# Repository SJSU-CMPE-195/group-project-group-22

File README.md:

# (Neuromorphic) Hardware Neural Network

Neuromorphic computing replicates brain structure and function directly in hardware. Unlike conventional processors, it uses parallel, event-driven processing for greater efficiency. Software-based spiking neural networks (SNNs) appear in autonomous control systems but carry high energy and resource costs. This project implements the SNN as a real analog circuit — a physical, transistor-level network built from discrete components on a breadboard or PCB — so the hardware itself is the AI player.

The fundamental building block is a **3-neuron control unit** implementing the integrate-and-fire model: an excitatory neuron and an inhibitory neuron both feed into a control (output) neuron. The excitatory neuron drives the control neuron to fire; the inhibitory neuron suppresses overfiring and improves signal stability. Each control unit produces one discrete game action. This scheme is scalable — Hit The Zone uses one 3-neuron control unit (one game input), and Pong uses two control units (six neurons total, one control unit per direction).

An ESP32 microcontroller acts as the analog bridge between the neuron circuit and the game software: it injects stimulus voltage into the excitatory neuron in response to game state, reads the control neuron's output voltage via ADC, and streams real-time voltage data to a Java application over USB serial at 115200 baud. The Java application detects neural spikes via rising-edge analysis and translates each spike one-to-one into a discrete game action.

A **Launcher** manages serial connections and serves as the home page for all programs. Two games are supported: **Hit The Zone** (3-neuron, single-channel) and **Pong** (6-neuron, dual-channel — Ch1 controls left, Ch2 controls right). A **Bidirectional Test** diagnostic tool is also included for verifying serial communication and signal integrity.

## Table of Contents

- [Team](#team)
- [Deliverables](#deliverables)
- [Prerequisites](#prerequisites)
- [Hardware](#hardware)
  - [Hardware Revisions](#hardware-revisions)
  - [Schematic](#schematic)
  - [PCB Design](#pcb-design)
  - [Bill of Materials](#bill-of-materials)
  - [Datasheets](#datasheets)
  - [Breadboard Assembly](#breadboard-assembly)
  - [PCB Assembly](#pcb-assembly)
  - [Flashing the ESP32](#flashing-the-esp32)
- [Running the Application](#running-the-application)
- [Configuration](#configuration)
- [Programs](#programs)
  - [Launcher](#launcher)
  - [Hit The Zone](#hit-the-zone)
  - [Pong](#pong)
  - [Bidirectional Test](#bidirectional-test)
  - [Shared Components](#shared-components)
- [Testing](#testing)
- [Project Structure](#project-structure)
- [License](#license)
- [References](#references)

---

## Team

**Project Number:** U32

**Project Title:** Hardware Neural Network

**Advisor:** Eric Vanuska — eric.vanuska@sjsu.edu

| Name             | Degree | GitHub                                               | Email                     |
|------------------|--------|------------------------------------------------------|---------------------------|
| Jonathon Fleming | BSCMPE | [@JellyF02](https://github.com/JellyF02)             | jonathon.fleming@sjsu.edu |
| Raymund Mercader | BSSE   | [@ray-sjsu](https://github.com/ray-sjsu)             | raymund.mercader@sjsu.edu |
| Andrew Neidhart  | BSCMPE | [@andrewneidhart](https://github.com/andrewneidhart) | andrew.neidhart@sjsu.edu  |
| Katrina Weers    | BSSE   | [@Trina-W](https://github.com/Trina-W)               | katrina.weers@sjsu.edu    |

[Spring 2026 CMPE Project Expo](https://www.sjsu.edu/cmpe/students/project-expo/2026-spring.php)

[Spring 2026 CMPE Project Roster](https://docs.google.com/spreadsheets/d/1CWvXRMa2uYdF89KqGeZLIvugnG1znIKHWkJCl6HlvxU/edit?gid=0#gid=0)

---

## Deliverables

The project poster provides a full overview of the hardware design, circuit theory, system architecture, and game demonstrations.

[Download PDF version](docs/deliverables/U32%20Hardware%20Neural%20Network.pdf)

---

## Prerequisites

**Software:**
- [Java JDK 17](https://docs.oracle.com/en/java/javase/17/install/overview-jdk-installation.html)
- [Arduino IDE](https://www.arduino.cc/en/software) (only needed to flash the ESP32)
- [Apache Maven 3.6+](https://maven.apache.org/install.html) and [Git](https://git-scm.com/install/) (only needed to build from source)

**Hardware:**
- ESP32 microcontroller connected via USB/Serial
- Neural network circuit assembled on breadboard or PCB (see [Hardware](#hardware))

---

## Hardware

### Hardware Revisions

Three physical builds were produced over the course of the project. The Breadboard Big, Breadboard Small, and PCB are functionally identical. See the [project poster](#deliverables) for full hardware design details.

| Revision         | Form Factor          | Neurons | Notes                                                                   |
|------------------|----------------------|---------|-------------------------------------------------------------------------|
| Breadboard Big   | Full-size breadboard | Up to 6 | Initial large-scale prototype                                           |
| Breadboard Small | Half-size breadboard | Up to 6 | Compact verification build                                              |
| PCB (V2)         | Custom KiCad PCB     | Up to 6 | Production form factor; functionally identical to all breadboard builds |

| Breadboard Big                                                                              | Breadboard Small vs. PCB                                                                                              |
|---------------------------------------------------------------------------------------------|-----------------------------------------------------------------------------------------------------------------------|
|  |  |

| PCB Board                                                               | PCB 3D Render                                                                   |
|-------------------------------------------------------------------------|---------------------------------------------------------------------------------|
|  |  |

---

### Schematic

Each neuron in the circuit is built around a **Schmitt trigger** — a comparator with hysteresis. Input voltage charges up slowly (integration), and when it crosses the upper threshold V_UT the output snaps sharply to saturation (the spike). It won't reset until voltage falls below the lower threshold V_LT. The dead band between the two thresholds prevents noise from causing false re-triggers, giving each neuron a clean, stable firing response — directly analogous to a biological action potential [1].

**Single Neuron V1** — the initial single-neuron proof-of-concept schematic.

Source file: [`hardware/schematics/Single-Neuron-V1-Schematic.asc`](hardware/schematics/Single-Neuron-V1-Schematic.asc) (LTspice)

---

**NeuronSynapseVersion7** — the final 3-neuron design used across all builds.

Source files: [`hardware/schematics/Neuron-Synapse-Version7-Schematic.asc`](hardware/schematics/Neuron-Synapse-Version7-Schematic.asc) (LTspice) and [`hardware/schematics/Neuron-Synapse-Version7-Kicad-Schematic.kicad_sch`](hardware/schematics/Neuron-Synapse-Version7-Kicad-Schematic.kicad_sch) (KiCad)

---

### PCB Design

KiCad project: [`hardware/pcb/PCB-Neuron-V2-Kicad-Project.kicad_pro`](hardware/pcb/PCB-Neuron-V2-Kicad-Project.kicad_pro)

---

### Bill of Materials

- [`hardware/bom/BOM breadboard.csv`](hardware/bom/BOM_breadboard.csv)
- [`hardware/bom/BOM_pcb.csv`](hardware/bom/BOM_pcb.csv)

---

### Datasheets

- [Espressif ESP32 Datasheet](hardware/datasheets-and-diagrams/Espressif-ESP32-Datasheet.pdf) [2]
- [ESP32 DevKitC Pinout Diagram](hardware/datasheets-and-diagrams/Espressif-ESP32-DevkitC-PinOut-Diagram.png) [3]

---

### Breadboard Assembly

These steps produce a single-channel build for **Hit The Zone**. The Pong extension at the end adds a second circuit for dual-channel support.

You will need the **NeuronSynapseVersion7** schematic (`hardware/schematics/`) open as a reference throughout.

**What you need:**
- Breadboard(s) and jumper wires
- All components listed in [`hardware/bom/BOM_pcb.csv`](hardware/bom/BOM_pcb.csv)
- A breadboard power supply module — powered by a USB battery bank or wall adapter
- An ESP32 microcontroller
- A USB cable to connect the ESP32 to your computer

---

**1. Set up power rails**

Mount the breadboard power supply module onto the breadboard and connect your USB battery bank or wall adapter. Set the output to **3.3V**. Verify that the positive (+) and negative (−) power rails along the breadboard are live before placing any components. The neuron circuit runs on 3.3V.

**2. Gather and place components**

Using the NeuronSynapseVersion7 schematic as your guide, place all components onto the breadboard. The schematic organizes the circuit into three neuron subcircuits — the excitatory neuron, the inhibitory neuron, and the control (output) neuron. Place and wire them one subcircuit at a time to keep the build manageable.

**3. Wire the neuron circuit**

Follow the NeuronSynapseVersion7 schematic section by section. Complete and double-check each subcircuit before moving to the next. Make sure all power and ground connections are secure throughout.

**4. Connect the ESP32**

The ESP32 does not need to sit on the breadboard — it connects to the circuit via jumper wires. Make the following connections (refer to the ESP32 DevKitC pinout [3] to locate these pins):

| ESP32 Pin     | Connects to                  | Purpose                    |
|---------------|------------------------------|----------------------------|
| GPIO34 (ADC6) | Control neuron output node   | Reads neuron spike voltage |
| GPIO25 (DAC1) | Excitatory neuron input node | Injects stimulus voltage   |
| GND           | Breadboard GND rail          | Shared ground              |

Optionally connect **GPIO2** to a status LED with a current-limiting resistor — the firmware will light it when the neuron output crosses the firing threshold.

Then plug the ESP32 into your computer via USB. This connection is for serial communication only — the breadboard power supply powers the circuit independently.

> **Single-channel build complete.** This is all that is needed to run **Hit The Zone**. Flash the ESP32 with `CHANNEL_COUNT 1` (see [Flashing the ESP32](#flashing-the-esp32)) and proceed to [Running the Application](#running-the-application).

---

**5. Pong extension — add a second control unit**

Pong requires two 3-neuron control units. Build a second complete NeuronSynapseVersion7 circuit on the same or a second breadboard, powered from the same power supply rails. Add the following connections to the ESP32:

| ESP32 Pin     | Connects to                         | Purpose                        |
|---------------|-------------------------------------|--------------------------------|
| GPIO35 (ADC7) | Second control neuron output node   | Reads RIGHT spike voltage      |
| GPIO26 (DAC2) | Second excitatory neuron input node | Injects RIGHT stimulus voltage |

Flash the ESP32 with `CHANNEL_COUNT 2` (see [Flashing the ESP32](#flashing-the-esp32)) to enable dual-channel mode.

---

### PCB Assembly

The PCB (`hardware/pcb/`) is functionally identical to all breadboard builds in a more compact form factor. Solder components using the NeuronSynapseVersion7 schematic as your reference — component values and connections are the same as the breadboard build.

The PCB has two 6-pin headers, **JP1** (left) and **JP2** (right), which expose power and signal connections. Both headers follow the same pin layout:

| Pin | Net    | Purpose                    |
|-----|--------|----------------------------|
| 1–2 | `+3V3` | Power supply input (3.3 V) |
| 3–4 | Signal | See below                  |
| 5–6 | `GND`  | Ground                     |

- **JP1** (input side) — pin 3 carries the inverted input signal; pin 4 is the direct signal input. Wire **ESP32 GPIO25 (DAC1)** to JP1 pin 4 to inject stimulus voltage.
- **JP2** (output side) — pins 3–4 are bridged on the same net and connect to the control neuron output circuit. Wire **ESP32 GPIO34 (ADC6)** to JP2 pin 3 (or 4) to read the spike voltage.

Power the PCB by connecting a **3.3 V source** to JP1 or JP2 pins 1–2, with **GND** on pins 5–6. The ESP32's onboard 3.3 V output pin can be used for this if the circuit current draw is within limits, or use the same breadboard power supply module approach with a USB battery bank or wall adapter.

---

### Flashing the ESP32

The firmware lives in `hardware/firmware/`. Two `.ino` files are provided — they are functionally identical except for the `CHANNEL_COUNT` parameter:

| `CHANNEL_COUNT` | Configuration                                 | Used by      |
|-----------------|-----------------------------------------------|--------------|
| `1`             | 3-neuron, single ADC channel (GPIO34)         | Hit The Zone |
| `2`             | 6-neuron, dual ADC channels (GPIO34 + GPIO35) | Pong         |

1. Open the desired `.ino` file in **Arduino IDE**:
   - `NeuralSerial_SingleChannel_3Neuron.ino`
   - `NeuralSerial_DualChannel_6Neuron.ino`
2. Confirm or set `CHANNEL_COUNT` near the top of the file:
   ```cpp
   // Set CHANNEL_COUNT to 1 for 3-neuron HitTheZone config.
   // Set CHANNEL_COUNT to 2 for 6-neuron Pong config.
   #define CHANNEL_COUNT 1
   ```
3. Select **Tools → Board → ESP32 Dev Module** and the correct **Tools → Port**.
4. Click **Upload**, then open the **Serial Monitor** at 115200 baud to confirm the board is sending data.

---

## Running the Application

Download the latest release from the [Releases page](https://github.com/SJSU-CMPE-195/group-project-group-22/releases). The release includes the Java application and the ESP32 firmware.

### Java Application

Two distribution formats are available:

**Standalone JAR** — a single `hardware-neural-network.jar` file. Requires Java 17+ already installed on your system.

```bash
java -jar hardware-neural-network.jar
```

**Bundled runtime** — a folder called `hardware-neural-network/` containing a `.exe` alongside `app/` and `runtime/` directories. Java is included — no separate installation needed. Run the `.exe` inside the folder.

This opens the **Launcher**, which is the home page for all programs.

**Building from source** (optional):

```bash
git clone https://github.com/SJSU-CMPE-195/group-project-group-22.git
cd group-project-group-22/software
mvn install
java -jar target/hardware-neural-network.jar
```

### Firmware

The release also includes the `.ino` firmware files for the ESP32. See [Flashing the ESP32](#flashing-the-esp32) for installation instructions.

---

## Configuration

No API keys or environment variables are required. The only configuration is the `CHANNEL_COUNT` firmware parameter described in [Flashing the ESP32](#flashing-the-esp32).

---

## Programs

**Summary Class Diagram**

---

### Launcher

The Launcher is the home page of the application. It provides two serial connection panels — one for Hit The Zone (single-channel) and one for Pong (dual-channel) — and buttons to open each program.

Connect your ESP32 device(s) in the Launcher before opening a program to enable the hardware neural network AI player. All programs are fully playable without hardware — Software AI players serve as the baseline for comparison, and the Hardware AI option will simply be grayed out when no device is connected.

**Class Diagram**

---

### Hit The Zone

A game where four players take turns hitting a ball as it passes through a target zone. The hardware SNN (using the 3-neuron, single-channel ESP32 firmware config) competes alongside two software AI bots and a human player.

**Hardware Setup**

**Players:**
- **Bot Alpha / Beta** — software AI players
- **Human** — press Space when the ball is inside the yellow zone to score a hit
- **Neural** — the ESP32 hardware neural network player

**Controls:**

| Key   | Action                          |
|-------|---------------------------------|
| Space | Hit the ball (when inside zone) |
| Esc   | Pause / unpause                 |
| R     | Reset the game                  |

**Stats tracked:** Hits (successful / total attempts), Accuracy (%), Hits/Pass (average hits per ball pass)

**Class Diagram**

---

### Pong

A Pong game where the hardware SNN competes as an AI paddle controller. The ESP32 (6-neuron, dual-channel config) reads two ADC channels — GPIO34 for LEFT and GPIO35 for RIGHT — and drives a single hardware AI player. Player types (Human / Hardware AI / Software AI Easy / Software AI Hard) are selected from the in-game toolbar.

**SNN Architecture**

Pong uses two 3-neuron control units (6 neurons total). Each control unit consists of an excitatory neuron, an inhibitory neuron, and a control (output) neuron — both the excitatory and inhibitory neurons feed into the control neuron, which fires when its membrane voltage V reaches threshold θ. One control unit drives LEFT, the other drives RIGHT.

The architecture diagram below shows the logical view: Ball X Position feeds a Directional Split Layer (Ball Left / Ball Right excitatory neurons), which drive an Output Layer (Paddle Left / Paddle Right control neurons). The red cross-inhibition connections — Ball Left inhibiting Paddle Right and vice versa — represent the inhibitory neurons in each control unit, ensuring only one direction fires at a time, producing one discrete paddle movement event per spike.

**Hardware Setup**

**Controls (Human player):**

| Key       | Action                                       |
|-----------|----------------------------------------------|
| ← / →     | Move paddle left / right                     |
| Esc       | Pause / unpause                              |
| R         | Reset the game (from pause menu)             |
| C         | Toggle constant ball speed (from pause menu) |
| 1 / 2 / 3 | Select ball speed level (from pause menu)    |

**Class Diagram**

---

### Bidirectional Test

A diagnostic tool for verifying serial communication between the ESP32 and the Java application. It receives both Launcher-managed connections (Hit The Zone and Pong) and lets you switch between them to inspect bidirectional data flow — useful for debugging firmware behavior or confirming signal integrity before running a game.

**Class Diagram**

---

### Shared Components

The `hardware` and `player` packages are shared across all programs. `hardware` handles serial connection management and neural signal processing. `player` provides the base player abstractions used by every game.

**Hardware Class Diagram**

**Player Class Diagram**

---

## Testing

### Running the Test Suite

```bash
cd software
mvn verify
```

This runs all unit, integration, and stress tests and generates a JaCoCo HTML coverage report at `software/target/site/jacoco/index.html`.

> Tests that instantiate Swing components require a display. On Linux, prefix with `xvfb-run --auto-servernum`.

**Useful variants:**

```bash
# Stress tests only (no display required)
mvn test -Dgroups=stress

# A single test class
mvn test -Dtest=NeuralSignalParserTest
```

### Coverage

The latest coverage report is uploaded as the **`jacoco-coverage-report`** artifact on every CI run — see [Actions](https://github.com/SJSU-CMPE-195/group-project-group-22/actions/workflows/ci.yml).

Full coverage details, per-package breakdown, and exclusion rationale are in [`docs/evaluation/coverage-report/README.md`](docs/evaluation/coverage-report/README.md).

### Stress Test Results

Documented in [`docs/evaluation/stress-test-results.md`](docs/evaluation/stress-test-results.md).

---

## Project Structure

```
group-project-group-22/
├── .github/
│   └── workflows/
│       └── ci.yml                                  # Build, test, and coverage reporting
├── docs/
│   ├── class-diagrams/                             # PNG class diagrams
│   │   ├── plantuml-diagrams/                      # PlantUML source (.puml)
│   │   ├── class-diagram-bidirectionaltest.png
│   │   ├── class-diagram-hardware.png
│   │   ├── class-diagram-hitthezone.png
│   │   ├── class-diagram-launcher.png
│   │   ├── class-diagram-player.png
│   │   ├── class-diagram-pong.png
│   │   └── class-diagram-summary.png
│   ├── deliverables/                               # Project poster (SVG + PDF)
│   ├── evaluation/                                 # coverage-report/ + stress-test-results.md
│   └── images/
│       ├── java-program/                           # Application screenshots
│       ├── neural-network-game-setups/             # Hardware + game configuration photos
│       ├── physical-hardware-builds/               # Build photos (breadboard, PCB)
│       ├── pong-game-snn-architecture-diagram.png
│       └── schmitt-trigger-diagram.png
├── hardware/
│   ├── bom/                                        # Bill of materials (CSV)
│   ├── datasheets-and-diagrams/                    # ESP32 datasheet and pinout diagram
│   ├── firmware/                                   # ESP32 Arduino firmware (single- and dual-channel) + archive/
│   ├── pcb/                                        # KiCad PCB V2 project + archive/
│   └── schematics/                                 # KiCad + LTspice schematics, PNGs + archive/
├── scripts/
│   └── generate-class-diagram.py                   # Generates PlantUML source from Java source
├── software/
│   └── src/
│       ├── main/java/.../
│       │   ├── bidirectionaltest/                  # Diagnostic tool — core/ + ui/
│       │   ├── hardware/                           # Serial + signal processing — serial/ + signal/
│       │   ├── hitthezone/                         # Hit The Zone game — ai/ + core/ + model/ + ui/
│       │   ├── launcher/                           # Launcher home page — core/ + model/ + ui/
│       │   ├── player/                             # Shared player abstractions — model/
│       │   └── pong/                               # Pong game — ai/ + core/ + model/ + ui/
│       └── test/java/.../                          # JUnit 5 + Mockito test suite + stress/ + testsupport/
├── tests/
│   └── README.md                                   # Test structure and instructions
├── .gitignore
├── LICENSE
├── README.md
├── SCHEDULE-195.md
├── icon.ico
└── pom.xml
```

---

## License

This project is licensed under the MIT License — see the [`LICENSE`](LICENSE) file for details.

> Distribution is subject to applicable San Jose State University intellectual property policies.
---

## References

[1] Hackatronic, "Schmitt Trigger Circuit Diagram, Working, Types & Applications," *Hackatronic*, 2023. [Online]. Available: https://www.hackatronic.com/schmitt-trigger-circuit-diagram-working-types-applications/. [Accessed: May 6, 2026].

[2] Espressif Systems, "ESP32 Series Datasheet," *Espressif Systems*, 2024. [Online]. Available: https://documentation.espressif.com/esp32_datasheet_en.pdf. [Accessed: May 6, 2026].

[3] Espressif Systems, "ESP32-DevKitC User Guide," *Espressif Documentation*, 2024. [Online]. Available: https://docs.espressif.com/projects/esp-dev-kits/en/latest/esp32/esp32-devkitc/user_guide.html. [Accessed: May 6, 2026].

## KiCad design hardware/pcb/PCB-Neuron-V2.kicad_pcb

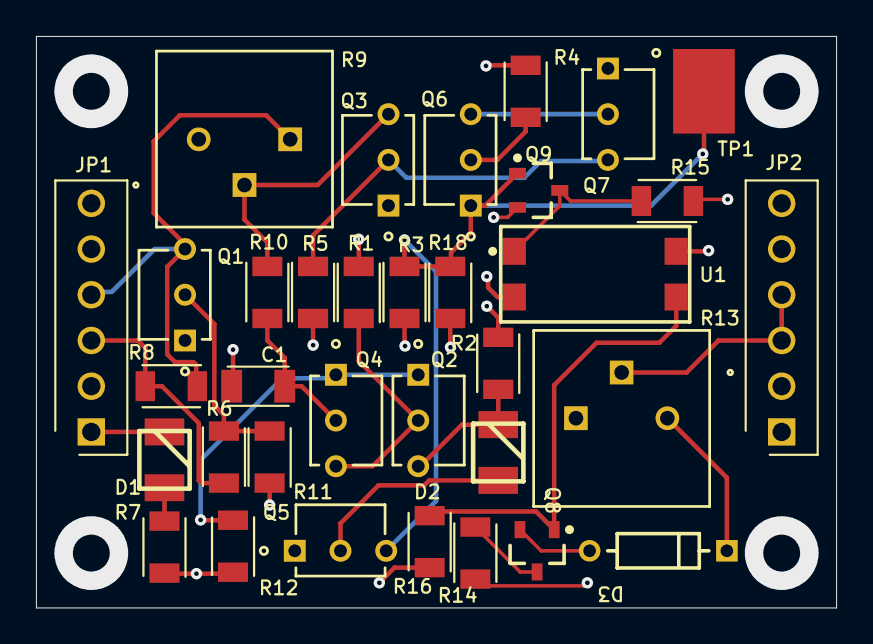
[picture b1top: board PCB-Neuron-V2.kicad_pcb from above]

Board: 4 copper layers, 44.5 x 31.8 mm, 34 parts (0 on the bottom side), 22 nets.

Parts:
C1: C3216X5R1E476M160AC; C1206
D1, D2: AA3528SESK/J3; 2-PLCC-RED
D3: 1N4148WT; FP-017AG-MFG
JP1, JP2: HEADER_6X1; HEADER1x6PITCH100
Q1, Q2, Q3, Q4, Q5, Q6, Q7: 2n2222a; 2n2222a-Footprint-1
Q8, Q9: 2N7002
R1, R6, R16: RNCF1206TKY10K0; R1206
R2, R5, R10: ERJ-8ENF2001V; R1206
R3, R11, R14, R15: 1k; R1206
R4: 100k; R1206
R7, R12: 330; R1206
R8: ERJ-8ENF2000V; R1206
R9: Bourns 3386P-1-104LF; Bourns 3386P-1-104LF-Footprint-1
R13: 3386P-1-504LF; 3386P-1-504LF-Footprint-1
R18: ERJ-8ENF1004V; R1206
TP1: 5016
U1: LTV-817S; LTST-LTV-817S-4_V

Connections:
+3V3: D1.2, JP1.1, JP1.2, JP2.1, JP2.2, R1.2, R2.2, R3.2, R4.2, R5.2, R14.2, R15.2, U1.4
FB: Q3.3, R9.2, R10.1
G12_E: Q2.1, Q4.1, R12.2
G23_GA: D2.2, Q2.3, R2.1
G23_GK: D2.1, Q5.2
GND: C1.1, JP1.5, JP1.6, JP2.5, JP2.6, Q1.1, Q3.1, Q5.1, Q7.1, Q9.2, R7.1, R11.1, R12.1, R16.1, R18.1, U1.2
NetD1_1: D1.1, R7.2
NetJP1_3: JP1.3, R6.2, R8.2
NetJP1_4: JP1.4, Q1.3, R8.1, R9.3
NetJP2_3: JP2.3, JP2.4, R13.2
NetQ1_2: Q1.2, R6.1, R11.2
NetQ6_2: Q6.2, R4.1
Q1_G: C1.2, Q4.2, R10.2
Q7_D: Q9.3, R15.1, U1.1
Q8_D: Q8.3, R14.1
Q8_DK: D3.1, R13.1
Q8_S: D3.2, Q8.2
Q12_G: Q2.2, Q4.3, R1.1
Q34_G: Q5.3, Q6.1, Q9.1, R3.1, R18.2, TP1.1
Q45_CG: Q6.3, Q7.2
Q56_G: Q3.2, Q7.3, R5.1
U_Q8_G: Q8.1, R16.2, U1.3

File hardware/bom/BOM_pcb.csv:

Line #,Name,Description,Designator,Quantity,Manufacturer 1,Manufacturer Part Number 1,Manufacturer Lifecycle 1,Supplier 1,Supplier Part Number 1,Supplier Unit Price 1,Supplier Subtotal 1

"","2n2222a","Bipolar (BJT) Transistor NPN 40 V 600 mA 250MHz 625 mW Through Hole TO-92","Q1, Q2, Q3, Q4, Q5, Q6, Q7","7","","","","","","",""
"","Bourns 3386P-1-104LF","100 kOhms 0.5W, 1/2W PC Pins Through Hole Trimmer Potentiometer Cermet 1.0 Turn Top Adjustment","R9","1","","","","","","",""
"","1k","1K OHM 1% 1/4W 1206","R3, R11, R14, R15","4","Panasonic","ERJ-8ENF1001V","Not Recommended for New Design","Mouser","667-ERJ-8ENF1001V","0.054","0.54"
"","100k","100K OHM 1% 1/4W 1206","R4","1","Panasonic","ERJ-8ENF1003V","Not Recommended for New Design","DigiKey","P100KFCT-ND","0.16","0.16"
"","330","330 OHM 1% 1/4W 1206","R7, R12","2","Panasonic","ERJ-8ENF3300V","Not Recommended for New Design","DigiKey","P330FCT-ND","0.16","0.32"
"","ERJ-8ENF2000V","200 OHM 1% 1/4W 1206","R8","1","Panasonic","ERJ-8ENF2000V","Not Recommended for New Design","DigiKey","P200FCT-ND","0.16","0.16"
"","ERJ-8ENF2001V","2K OHM 1% 1/4W 1206","R2, R5, R10","3","Panasonic","ERJ-8ENF2001V","Not Recommended for New Design","Mouser","667-ERJ-8ENF2001V","0.16","0.48"
"","ERJ-8ENF1004V","1M OHM 1% 1/4W 1206","R18","1","Panasonic","ERJ-8ENF1004V","Unknown","","","",""
"","HEADER_6X1","HEADER VERT 6POS .100 TIN","JP1, JP2","2","Wurth Elektronik","61300611121","Unknown","Mouser","710-61300611121","0.34","0.68"
"","1N4148WT","Rectifier Diode, 1 Phase, 1 Element, 0.15A, 100V V(RRM), Silicon","D3","1","onsemi","1N4148TR","Volume Production","Mouser","512-1N4148TR","0.1","0.1"
"","2N7002","MOSFET N-CH 60V 115 mA","Q8, Q9","2","onsemi","2N7002","Volume Production","Mouser","512-2N7002","0.59","1.18"
"","3386P-1-504LF","Cermet Not Linear VERTICAL Trimmer Potentiometer ?10% 280deg 500mW 85C","R13","1","Bourns","3386P-1-504LF","Volume Production","Mouser","652-3386P-1-504LF","1.22","1.22"
"","5016","PC TEST POINT COMPACT SMT","TP1","1","Keystone","5016","Volume Production","DigiKey","36-5016CT-ND","0.26","0.26"
"","AA3528SESK/J3","LED Red 2.2V 20mA","D1, D2","2","Kingbright","AA3528SESK/J3","Volume Production","DigiKey","754-1771-1-ND","0.54","1.08"
"","C3216X5R1E476M160AC","CER 47uF 25V X5R 1206 2.082mOhm","C1","1","TDK","C3216X5R1E476M160AC","Volume Production","DigiKey","445-8047-1-ND","0.89","0.89"
"","LTV-817S","LTV Series Single Channel 35 V 5000 Vrms Transistor Output Optocoupler SMT-DIP-4","U1","1","Lite-On","LTV-817S","Volume Production","Mouser","859-LTV-817S","0.26","0.26"
"","RNCF1206TKY10K0","RES 10K OHM 0.01% 1/4W 1206","R1, R6, R16","3","Stackpole Electronics","RNCF1206TKY10K0","Volume Production","Mouser","708-RNCF1206TKY10K0","1.65","4.95"

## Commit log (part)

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2026-02-13 Setup directories for hardware and software teams
2026-02-22 Update .gitignore to exclude certain Java and Intellj files
2026-02-22 Implement basic sofftware poc test game
2026-03-11 Refactor PoC (move to own SRC folder). Add new features.
    Keybind controls.
    Continuous play.
    Running total with accuracy %.
    Reset button.
2026-03-11 Setup skeletons for pong game with player classes
2026-03-12 Move PoC_HitTheZone to meet maven standard
2026-03-12 Add parent pom.xml
2026-03-12 Add JUnit 5 to maven project
2026-03-12 Add boilerplate code for PoCTest.java. Change variable visibility, so PoC is testable.
2026-03-12 Implement function testRightWallBounce() to verify ball reverses direction at right wall
2026-03-12 Implement testResetFunctionality() to verify all counters clear on reset
2026-03-12 Implement testPauseLogic() to verify ball position freezes when paused
2026-03-12 Add headless constructor to PoC_HitTheZone to support unit testing
2026-03-12 Remove placeholder fail() calls from PoCTest
2026-03-12 Update testRightWallBounce() to use WIDTH const instead of gamePanel.getWidth()
2026-03-12 Generalize player package. Implement HumanPlayer class, and Interfaces (GameState, Action, PlayerType)
2026-03-13 Update parent and child pom.xml to add JUnit5
2026-03-13 Add PongAction and PongState core models
2026-03-13 Implement PongSoftwareAI "baseline" model
2026-03-13 Create BaseSignalSource interface for hardware and software simulations
2026-03-15 Implement SerialDevice interface
2026-03-15 Implement SerialConnectionManager to manage serial devices
2026-03-15 Implement NeuralSignalParser to convert ADC to voltage
2026-03-15 Update pom.xml to include mockito for JUnit tests
2026-03-17 Define PoC game Action and State
2026-03-18 Implement testAdcBounds() to verify max ADC value maps to 3.3V and min ADC val maps to 0.0V
2026-03-19 Implement testMalformedData() to verify incomplete, non-numeric, blank, and null values return 0.0
2026-03-19 Implement setUp() to reinitialize NeuralSignalParser before each test to prevent voltage history leaks
2026-03-19 Implement testConnectionSuccessAndVoltageRead()
2026-03-19 Fix testMissingHardwareHandling() to verify connect() is called twice to account for reconnection attempt
2026-03-19 Implement testNoCompatibleHardware() to verify connect() returns false and getNextLine() returns null when no device is found
2026-03-19 Implement testDisconnect() to verify closePort() is called exactly once when disconnecting from hardware
2026-03-19 Implement HitTheZone Software AI using new Player models
2026-03-19 Rewrite HitTheZone to support new Player models. Add two software and one human player.
2026-03-22 Implement Team, Prerequisites, and Installation Steps
2026-03-22 Implement Configuration and Steps to run Application
2026-03-22 Implement Project Structure
2026-03-22 Update "Clone the repository" in Installation Steps
2026-03-22 Update spacing and list items for Prerequisites
2026-03-22 Implement HitTheZoneHardwareAI
2026-03-22 Update PoC_HitTheZone to support hardware and support PoCTest
2026-03-22 Update README description
2026-03-22 Update Maven version in Software Prereqs
2026-03-22 Add try/catch to RealSerialDevice and SerialConnectionManager
2026-03-23 More closely matches physical circuit values
2026-03-23 Update poc-screenshot and README descriptions, Java version, and running PoC command
2026-03-24 Add HitTheZoneHardwareAITest.java
2026-03-24 Add TODO for refactoring PoCTest
2026-03-25 Implement HitTheZoneHardwareAITest setUp()
2026-03-25 Implement basic action mapping tests for HitTheZoneHardwareAITest
2026-03-25 Implement metadata tests
2026-03-27 Refactor pom.xml
2026-03-28 Create BidirectionalTest.ino ESP32 firmware for testing bidirectional communication
2026-03-28 Create BidirectionalTest.java program for testing bidirectional communication and voltage injection
2026-04-08 Add files via upload
    Fixed issue with MOSFET (M1)
2026-04-12 Upload ESP32 firmware for 3 neuron (single-channel) and 6 neuron (dual-channel) config
2026-04-13 Full Pong Game v1 with scoreboard and player selection
2026-04-14 Add mouse events in Pong pause menu
2026-04-14 Switch to two row layout for COMM connection in Launcher
2026-04-16 MOSFET rewiring
2026-04-16 Implement CI/CD. Minor fix to Launcher.
2026-04-16 BidirectionalTest: Fix UI bugs in pause logic
2026-04-16 Read raw voltage only. Remove software test artifacts from firmware.
2026-04-16 Rename NeuronSynapseVersion5.jpg to NeuronSynapseVersion7.jpg
2026-04-17 Physical PCB images/progress
2026-04-18 Bodging new wires
2026-04-18 Add % coverage report in CI/CD test coverage
2026-04-18 updated pcb & sch files
    original PCB design schematic and board had mosfet inverted
2026-04-18 Implement setUp(), tearDown(), and launcherFrameIsVisible()
2026-04-18 Implement launcherContainsPong() and launcherContainsHTZ() panel tests
2026-04-18 Implement closing window test
2026-04-18 Add PongGameTest boilerplate
2026-04-18 Implement setup/teaar down for pong game test suite
2026-04-18 added ball physics tests
2026-04-18 Implement scoring tests
2026-04-19 Add PongToolbarTest boilerplate
2026-04-19 Implement construction and before each for PongToolbar Suite
2026-04-19 Implement Lock/unlock during game tests
2026-04-19 Implement HardwareSignalSourceTest
2026-04-19 Implement SerialConnectionManager tests
2026-04-19 Edit hardwaresignalsource and neuralsignalparser tests formatting
2026-04-19 Implement HardwareAIPlayer tests
2026-04-19 Implement PlayerType tests
2026-04-19 Edit keyTypedIsNoOp() test
2026-04-19 Implement Scoreboard tests
2026-04-19 Implement PlayerVariantTest
2026-04-19 Remove unused import from PongGameTest
2026-04-19 Implement PongHardwareAI tests
2026-04-19 Implement PongState tests
2026-04-19 Implement HitTheZone tests
2026-04-19 Add new PoCTest files
2026-04-19 JaCoCo exclusions to focus on core functionality coverage
2026-04-19 Implement HitTheZoneHardwareAI tests
2026-04-19 Add Stress Testing and update docs directory (to point to coverage report and stress testing)
2026-04-19 Restructure SerialConnectionManager and Implement new tests
2026-04-19 Implement annotation logic for excluding specific functions from Jacoco coverage report
2026-04-20 UI enhancements to Launcher and BidirectionalTest. Update existing unit tests.
2026-04-20 Update README.md for version release
2026-04-20 Rename Synapses.csv to PCB BOM
2026-04-20 Update README.md for formatting enhancements
2026-04-24 Add ConnectionStatusPanel to child programs
2026-04-24 Add VoltageInjector class
2026-04-24 Refactor Launcher and its links to PongGame and HitTheZone.
2026-04-24 Fix bug where bidirectionaltest disconnects COMM device after shutdown
2026-04-24 HTZ: Convert single-score to multiple-score while in zone
2026-04-24 Disable EMA config (pass raw voltage)
2026-04-24 HTZ initial config with debug logs
2026-04-24 Implement pub-sub architecture for bidirectionaltest to simultaneously run multiple programs
2026-04-24 Add boilerplate and TODO tests
2026-04-24 Add exclusions for swing UI classses
2026-04-28 Implement setBallSpeed(), setZoneWidth(), createDefaultPlayers(), zoneStart() tests + reordered PoCTest.java file
2026-04-28 Refactor returnsIdleWhenNeitherFires() and idleJustBelowDefaultThreshold() to reflect updated hardware threshold config
2026-04-29 Implement new HitTheZoneHardwareAI tests
2026-04-29 Implement new tests for and reorder HardwareSignalSource
2026-04-29 Implement new PongGameTest tests
2026-04-30 Implement SerialConnectionManagerTest suite
2026-04-30 UI/UX enhancements in navigation for bidirectionaltest voltage injection panels
2026-04-30 Launcher: Add channel count check when connecting ESP32s
2026-04-30 BidirectionalTest: Fix UI bug for missing Ch 2 mode label
2026-04-30 Launcher: Hide already connected COMM ports from dropdown menu
2026-04-30 Move some methods in SerialConnectionPanel to SerialConnectionManager
2026-04-30 Version 1: Pong hardware-integration with 6 neurons
2026-05-01 PongGame: Hardware only controls paddle if moving towards it
2026-05-01 Rework spike detection for HitTheZone and PongGame
2026-05-01 HitTheZone: Fix bug on voltage injection while paused
2026-05-01 PongGame config changes
2026-05-01 BidirectionalTest - Fix bug with voltage injector panel flickering
2026-05-01 Launcher: Update SerialConnectionPanel UI to be more descriptive. Force disconnect for wrong devices.
2026-05-01 Refactor HitTheZone by UI and core extractions
2026-05-01 Launcher: Add advanced settings (voltage injection, threshold) for COMM ports
2026-05-01 Refactor Launcher by UI and core extractions
2026-05-01 Pong: Change ball speed and difficulties
2026-05-01 Move Pong Scoreboard logic to core package
2026-05-01 Move classes into their own relevant subpackages
    Testing setup part 1 - Move pong classes into their own subpackages
    Testing setup part 2 - Move hitthezone classes into their own subpackages
    Testing setup part 3 - Rename sandbox package to hitthezone package. Rename PoC_HitTheZone to HitTheZoneGame
    Testing setup part 4 - Move Launcher classes into their own subpackage
    Testing setup part 5 - Move player classes into their own subpackage
    Testing setup part 6 - Move hardware classes into their own subpackage
2026-05-01 Launcher: Update ActiveDeviceVoltageInjector for validation checks
2026-05-01 Disable voltage injection logs. Refactor Launcher (text, behavior on window height change)..
2026-05-01 Fix bug in SerialConnectionPanel with stale COMM ports caused by USB disconnects
2026-05-01 Change Launcher height from 520 to 620 for bigger log section
2026-05-03 Implement testsupport
2026-05-03 Initialize new test suite boilerplate, restructure test directory
2026-05-03 Implement ActiveDeviceVoltageInjectorTest testing suite
2026-05-03 Implement pong/core test suites
2026-05-03 Implement hitthezone/core testing suites
2026-05-04 Implement HardwareSignalSource test
2026-05-04 Implement NeuralSignalParserTest suite
2026-05-04 Implement pong/ai testing suites
2026-05-04 Implement hitthezone/ai test suites
2026-05-04 Implement hitthezonegame test suite
2026-05-04 Implement player test suites
2026-05-04 Remove TODOs from completed test suites
2026-05-05 Implement launcher ui tests + document coverage exclusion
2026-05-05 Implement exclusions for launcher test suite
2026-05-05 Implement hitthezone/ui test suites
2026-05-05 Implement PongGame test suite
2026-05-05 Update stress tests to use simulated hardware disconnects/reconnects and traffic scenarios
2026-05-05 Remove PlayerTypeTest test method
2026-05-05 Move and add screenshots in docs/images/
2026-05-05 Add MIT license
2026-05-05 Organize hardware/firmware directory
2026-05-05 Add ESP32 datasheet and pin-out diagram
2026-05-05 Organize hardware/pcb folder. Move Kicad Schematic to hardware/schematics.
2026-05-05 Initial commit of class diagram script and workflow
2026-05-06 Update class diagram summary generation + Add .png image generation
2026-05-06 Add new documentation. Fix workflows. Update .gitignore to exclude autogenerated diagrams.
    Update .gitignore to exclude autogenerated class diagrams
    Update README.md and LICENSE
2026-05-06 Fix workflow bug when diagrams are not committed when directory does not exist.
2026-05-06 Update README.md to include missing class diagrams
2026-05-06 Tests: Add mockitoAwtSupport for LauncherProgramRegistryTest
2026-05-06 Update JaCoCo coverage report to latest workflow run
2026-05-06 Update README.md team section to algin with expo spreadsheet
2026-05-06 Fix U32 Hardware Neural Network poster .svg
2026-05-07 README.md: Major enhancements to instructions + tweaks + references
    Add extra link to SJSU Spring 2026 CMPE Project Expo
    Update README.md to be more consistent and correct.
    Rewrite breadboard and PCB assembly instructions with more detail.
    Add references to external datasheets and diagrams
2026-05-07 Enhancements to README.md. Update downstream .md files to be up to date.
    Delete SCHEDULE-195.md
    Update stress test documentation
    Update tests README.md
